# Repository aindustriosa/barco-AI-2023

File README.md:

# Barco Solar AI-023 A Industriosa
Barco Solar AI-023 A Industriosa

Hemos creado un barco impreso en 3d para participar en la <a href="http://regatasolar.org" target="_blank">Regata Solar de Marine Instruments</a>. Esta vez un trimaran de unos 4Kg de peso y un volumen total de 12 litros.

Se ha diseñado integramente en Cinema 4D, con subdivisión de superficies (curvas Nurbs).

Una vez modelado, se han dividio en 32 piezas para imprimir, secciones de hasta 250x250x200mm y exportado a STL. Para optimizar la impresión intentamos que cada sección no tardase más de 10 horas en imprimirse, para intentar imprimir por el dia y dormir por la noche :P El software de slicer usado es el Simplify3D y la impresora una Ender 5 Plus.

Evitanto el uso de soportes a la hora de imprimir se han hecho algunas secciones que finalmente se pegan para poder imprimir sobre el lado más plano y evitar luego el postprocesado.

Una vez impresas las piezas, y para facilitar la rigidez a la hora de pegarlas, se han hecho unas secciones en cada pieza para pegar y encajar unos pequeños tubos impresos de unos 10x10x50mm. Se ha pegado todas las partes con pegamento para modelismo comprado en bazar chino, tarda unas 4 horas en secar y quedan las piezas muy rígidas. En las zonas que por sharping de las piezas hizo falta se relleno de masilla para carrocerías de Ceys. 

Para darle el acabado final, una vez pegadas todas las piezas, se ha aplicado imprimación de color blanco y posteriormente una mano de Epoxi. En el montaje, en las zonas más irregulares se le aplicó un poco de lijado.

Para encajar las partes de electrónica al barco, así como el soporte de la placa solar, se han usado unos insertos de M5 y M3 aplicados con solador, que evitan el uso de tuercas y hacen que las zonas de enrosque queden bien sujetas.

Para las tapas se ha usado goma Eva cortado en laser para hacer las zonas de unión impermeables.

## Electrónica

Hemos intentado hacer una nueva PCB partiendo de un Attiny1614. Se ha diseñado la pcb en KiCAD, integrando un sensor INA219 para la optimización del voltaje y potencia de la placa solar basandonos en la propuesta de <a href="https://github.com/aindustriosa/Solar_MPPT_board" target="_blank">A Industriosa</a> del año 2019.

Con los limites de potencia y memoria del Attiny1614, hemos implementado el uso del sensor así como un divisor de voltaje para leerlo via VREF. Los mensajes enviados desd eel mando RC al receptor, son procesados por el microcontrolador y en caso de exigirle una velocidad mayor al 30% entra en modo automático, y prioriza el rendimiento que este generando la placa solar en ese momento a optener la velocidad optima sin permitir la caida de potencia por un exceso del rendimiento de la placa solar.

## Materiales

8x PETG 1Kg Blanco 1.75mm (<a href="https://www.amazon.es/dp/B08C4YP5RS/ref=twister_B08HSFRV2M?_encoding=UTF8&th=1" target="_blank">Amazon</a>)

1x Smartfil FLEX - Filamento Flexible (<a href="https://www.smartmaterials3d.com/flex-filamento#/1-tamano-s_330g/26-diametro-175_mm/29-color-sapphire" target="_blank">Smart Materials 3D</a>)
  
3x Tubos cuadrados de 10x10x500mm - <a href="https://www.clipcarbono.com/es/home/947-tubo-exterior-cuadrado-10x10-mm-interior-cuadrado-8x8-mm-de-fibra-de-carbono-longitud-1000-mm.html" target="_blank">Tubo cuadrado, exterior (10x10 mm.) - interior (8x8 mm.) de fibra de carbono - Longitud 1000 mm.</a> Cortesía de <a href="https://www.clipcarbono.com" target="_blank">ClipCarbono</a>

1x Castropox 4307/1209 Resina Epoxi de usos generales (<a href="https://www.castrocompositesshop.com/es/resinas/1099-resina-epoxi-castropox-43071209.html" target="_blank">Castro Composites</a>)

1x Masilla Carrocerias Ceys (<a href="https://www.amazon.es/Desconocido-M59016-Adhesivo-masilla-carrocerias/dp/B00ITVXML6" target="_blank">Amazon</a>)

3x Imprimación Plástico (<a href="https://www.amazon.es/MTN-IMPRIMACIÓN-PLÁSTICOS-400-ML/dp/B00WG2K6W2/ref=sr_1_15?__mk_es_ES=ÅMÅŽÕÑ&crid=2E2QZXNCDXAI6&keywords=imprimacion&qid=1655512005&sprefix=imprimacion%2Caps%2C124&sr=8-15" target="_blank">Amazon</a>)

1x soporte helice y timón (<a href="https://es.aliexpress.com/item/32901476708.html" target="_blank">Aliexpress</a>)

100x Inserto roscado M3 (<a href="https://www.amazon.es/gp/product/B08BCRZZS3/ref=ppx_yo_dt_b_asin_title_o00_s00?ie=UTF8&th=1" target="_blank">Amazon</a>)

6x Inserto roscado M5 (<a href="https://www.amazon.es/gp/product/B07YSVXWS8/ref=ppx_yo_dt_b_asin_title_o00_s00?ie=UTF8&th=1" target="_blank">Amazon</a>)

1x Acoplamiento Motor 4x5mm (<a href="https://www.amazon.es/gp/product/B09LV3KD4H/ref=ppx_yo_dt_b_asin_title_o05_s00?ie=UTF8&th=1" target="_blank">Amazon</a>)

1x Motor NTM Prop Drive 28-30 800KV (<a href="https://hobbyking.com/es_es/propdrive-v2-2830-800kv-brushless-outrunner-motor.html" target="_blank">Hobbyking</a>)

1x Turnigy Multistart 20A V2 ESC (<a href="https://hobbyking.com/es_es/turnigy-multistar-20a-v2-esc-with-blheli-and-4a-lbec-2-6s.html" target="_blank">Hobbyking</a>)

## Enlaces

- <a href="http://regatasolar.org" target="_blank">Regata Solar de Marine Instruments</a>
- <a href="https://www.clipcarbono.com" target="_blank">ClipCarbono</a>
- <a href="http://aindustriosa.org" target="_blank">A Industriosa</a>

Proxecto patrocinado por Xunta de Galicia e Amtega Axencia para a Modernización Tecnolóxica

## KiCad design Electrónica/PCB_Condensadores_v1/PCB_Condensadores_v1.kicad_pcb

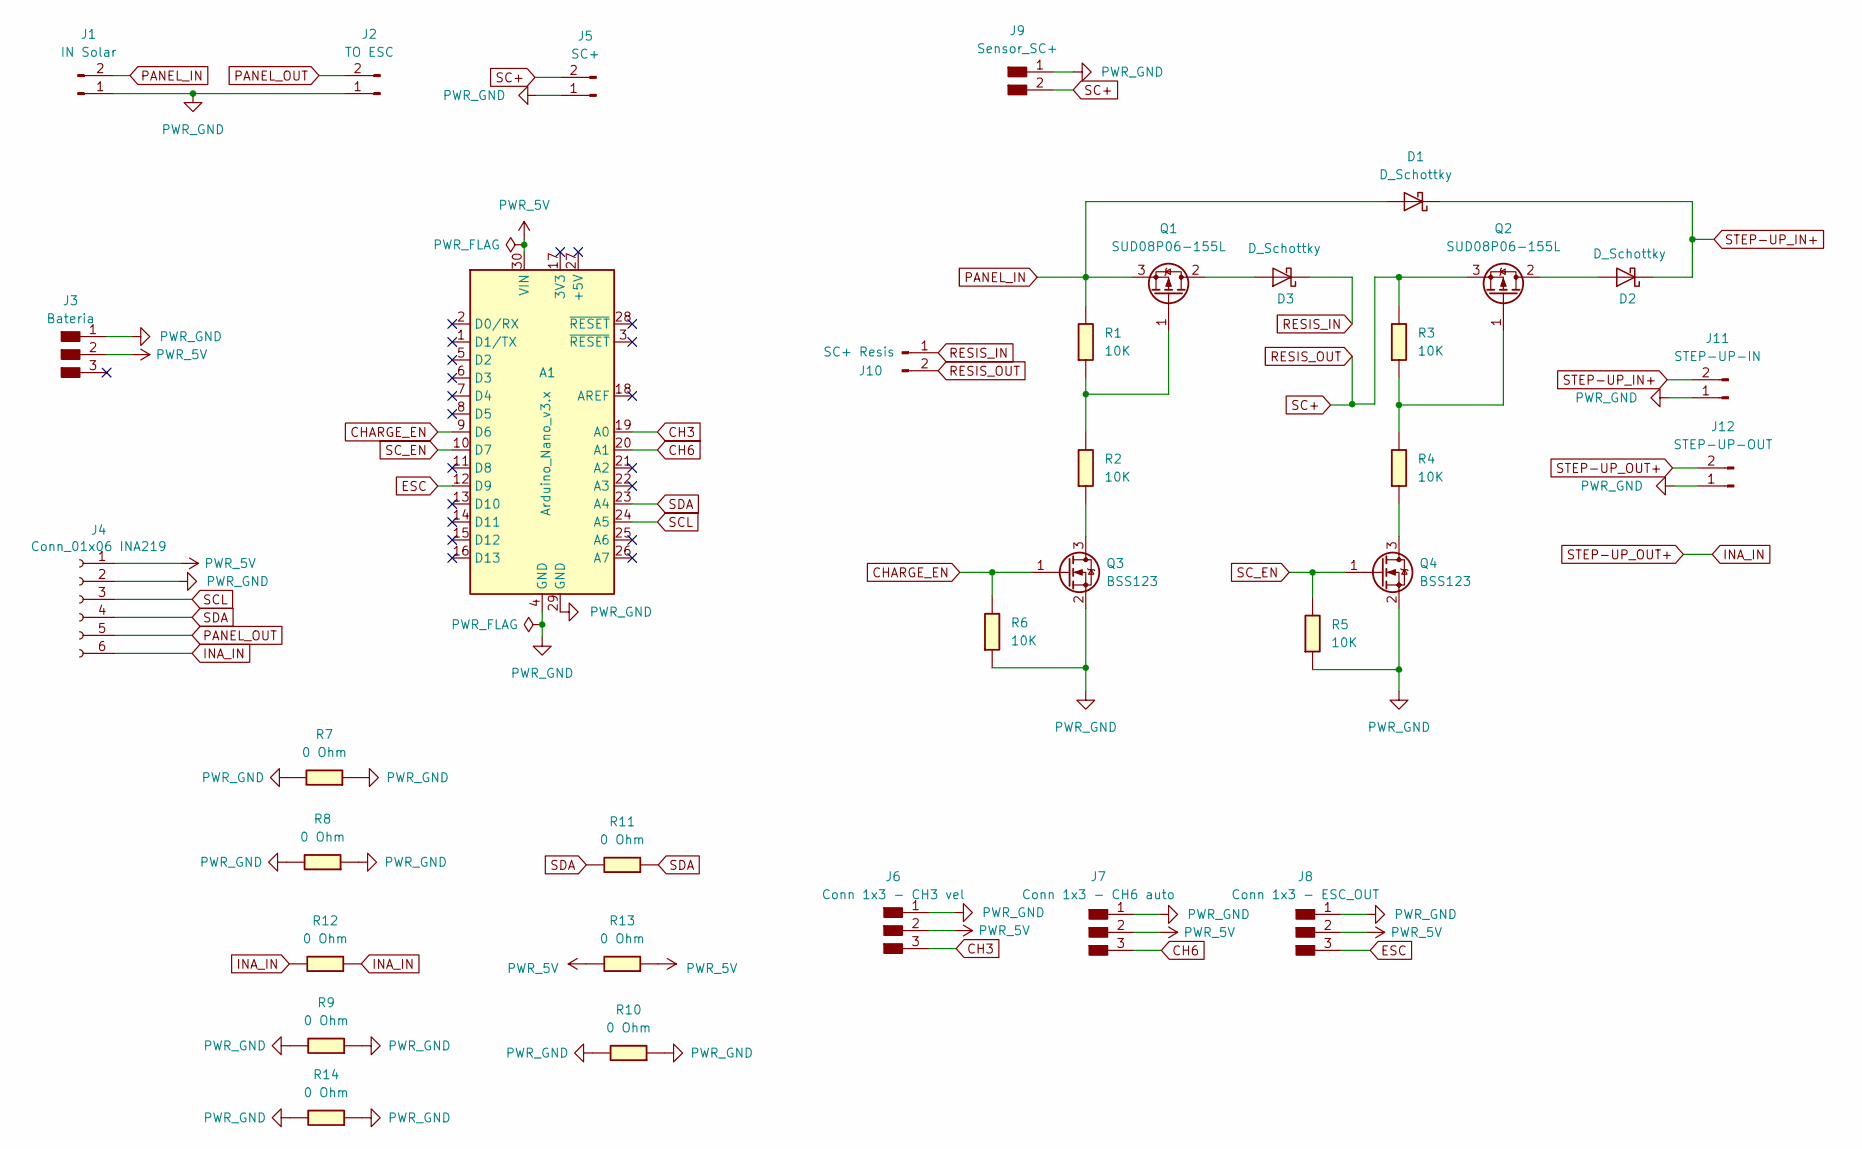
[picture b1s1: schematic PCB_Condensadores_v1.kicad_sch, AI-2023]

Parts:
A1: Arduino_Nano_v3.x; Arduino_Nano
D1, D2, D3: D_Schottky; D_SMC
J1: IN Solar; AMASS_XT60-F_1x02_P7.20mm_Vertical
J2: TO ESC; AMASS_XT60-M_1x02_P7.20mm_Vertical
J3: Bateria; PinHeader_1x03_P2.54mm_Vertical_THT_D1mm
J4: Conn_01x06 INA219; PinHeader_1x06_P2.54mm_Vertical_THT_D1mm; DIGIKEY_PN SAM1213-06-ND
J5: SC+; AMASS_XT60-M_1x02_P7.20mm_Vertical
J6: Conn 1x3 - CH3 vel; PinHeader_1x03_P2.54mm_Vertical_THT_D1mm
J7: Conn 1x3 - CH6 auto; PinHeader_1x03_P2.54mm_Vertical_THT_D1mm
J8: Conn 1x3 - ESC_OUT; PinHeader_1x03_P2.54mm_Vertical_THT_D1mm
J9: Sensor_SC+; PinHeader_1x02_P2.54mm_Vertical_THT_D1mm
J10: SC+ Resis; AMASS_XT60-M_1x02_P7.20mm_Vertical
J11: STEP-UP-IN; AMASS_XT60-M_1x02_P7.20mm_Vertical
J12: STEP-UP-OUT; AMASS_XT60-F_1x02_P7.20mm_Vertical
Q1, Q2: SUD08P06-155L; TO-252-2
Q3, Q4: BSS123; SOT-23
R1, R2, R3, R4, R5, R6: 10K; R_1206
R7, R8, R9, R10, R11, R12, R13, R14: 0 Ohm; R_1206

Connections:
CH3: A1.19 (A0), J6.3
CH6: A1.20 (A1), J7.3
CHARGE_EN: A1.9 (D6), Q3.1 (G), R6.1
ESC: A1.12 (D9), J8.3
INA_IN: J4.6, J12.2, R12.1, R12.2
unnamed: D2.2 (A), Q2.2 (D)
unnamed: D3.2 (A), Q1.2 (D)
unnamed: Q1.1 (G), R1.2, R2.1
unnamed: Q2.1 (G), R3.2, R4.1
unnamed: Q3.3 (D), R2.2
unnamed: Q4.3 (D), R4.2
PANEL_IN: D1.2 (A), J1.2, Q1.3 (S), R1.1
PANEL_OUT: J2.2, J4.5
PWR_5V: A1.30 (VIN), J3.2, J4.1, J6.2, J7.2, J8.2, R13.1, R13.2
PWR_GND: A1.4 (GND), A1.29 (GND), J1.1, J2.1, J3.1, J4.2, J5.1, J6.1, J7.1, J8.1, J9.1, J11.1, J12.1, Q3.2 (S), Q4.2 (S), R5.2, R6.2, R7.1, R7.2, R8.1, R8.2, R9.1, R9.2, R10.1, R10.2, R14.1, R14.2
RESIS_IN: D3.1 (K), J10.1
RESIS_OUT: J5.2, J9.2, J10.2, Q2.3 (S), R3.1
SCL: A1.24 (A5), J4.3
SC_EN: A1.10 (D7), Q4.1 (G), R5.1
SDA: A1.23 (A4), J4.4, R11.1, R11.2
STEP-UP_IN+: D1.1 (K), D2.1 (K), J11.2

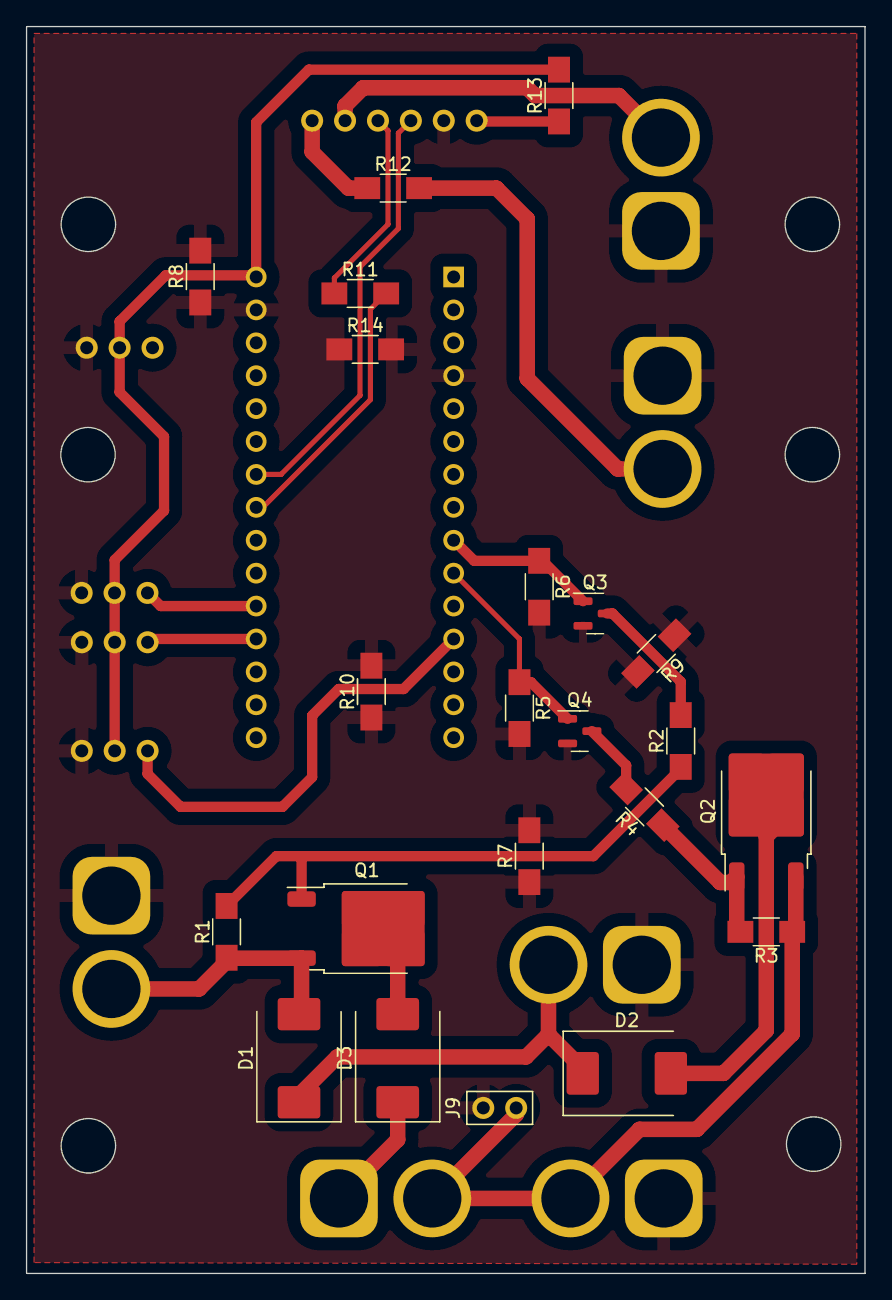
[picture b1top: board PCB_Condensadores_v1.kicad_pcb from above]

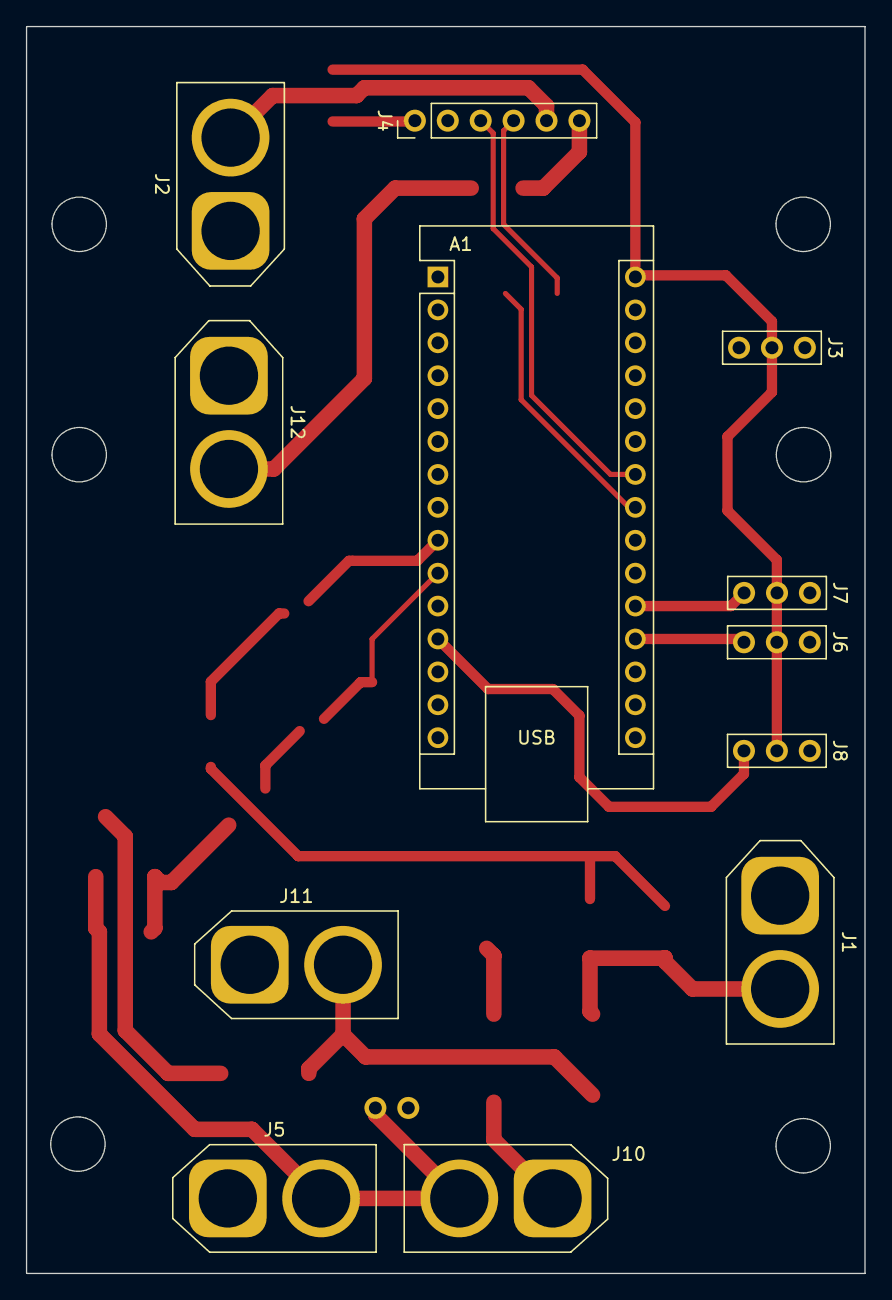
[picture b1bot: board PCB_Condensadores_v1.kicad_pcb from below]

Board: 2 copper layers, 64.7 x 96.2 mm, 34 parts (12 on the bottom side), 21 nets.

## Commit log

2023-06-18 files
